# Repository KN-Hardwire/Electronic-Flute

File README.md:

<div align="center">

# Electronic Flute

### *This repository present HARDWIRE student club [AGH University of Cracow](https://en.wikipedia.org/wiki/AGH_University_of_Krak%C3%B3w) Electronic Flute project.*

---

<br />
<em>Watch the video on our YouTube channel to see how it works!</em>

---

</div>

## Programming and assembly

Please refer to guides in each folder for details.

## Playing the flute

All the officially supported note are listed inside the [Fingering Chart](./Fingering_Chart.md), though you should be able to play the instrument just like a standard [recorder flute](https://en.wikipedia.org/wiki/Recorder_(musical_instrument)).

---
<div align="center">
  <sub>Electronic Flute • KN-Hardwire</sub>
</div>

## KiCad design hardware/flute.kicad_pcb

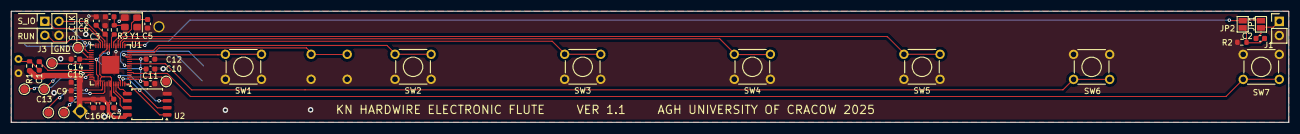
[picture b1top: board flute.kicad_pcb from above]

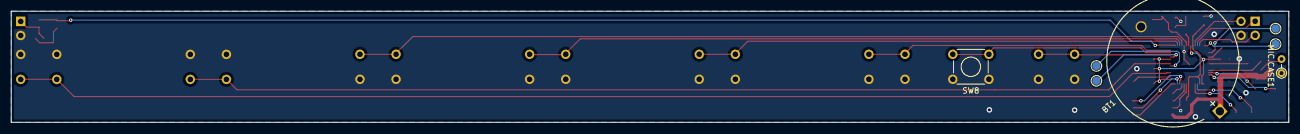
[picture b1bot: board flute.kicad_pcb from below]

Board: 2 copper layers, 230.0 x 20.0 mm, 47 parts (7 on the bottom side), 39 nets.

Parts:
BT1: Battery_Cell; BatteryHolder_MYOUNG_BS-07-A1BJ001_CR2032
C1, C2, C3, C10: 1uF; C_0603_1608Metric
C4, C7, C8, C9, C11, C12, C13, C14, C15, C16: 0.1uF; C_0603_1608Metric
C5, C6: 15pF; C_0603_1608Metric
J1: Conn_01x02; PinHeader_1x02_P2.54mm_Vertical
J3: Conn_01x04; PinHeader_2x02_P2.54mm_Vertical
JP1: COUPLING; SolderJumper-2_P1.3mm_Open_Pad1.0x1.5mm
JP2: NO_COUPLING; SolderJumper-2_P1.3mm_Open_Pad1.0x1.5mm
MIC.CASE1: R; R_Axial_DIN0204_L3.6mm_D1.6mm_P2.54mm_Vertical
R1: 2.2K; R_0603_1608Metric
R2: 100k; R_0603_1608Metric
R3: 1k; R_0603_1608Metric
SW1: C; SW_TH_Tactile_Omron_B3F-100x
SW2: D; SW_TH_Tactile_Omron_B3F-100x
SW3: E; SW_TH_Tactile_Omron_B3F-100x
SW4: F; SW_TH_Tactile_Omron_B3F-100x
SW5: G; SW_TH_Tactile_Omron_B3F-100x
SW6: A; SW_TH_Tactile_Omron_B3F-100x
SW7: H; SW_TH_Tactile_Omron_B3F-100x
SW8: OCTAVE?; SW_TH_Tactile_Omron_B3F-100x
TP2, TP3, TP4, TP5, TP6, TP7, TP8, TP9, TP10, TP11, TP12: TestPoint; TestPoint_Pad_D1.5mm
U1: RP2040; QFN-56-1EP_7x7mm_P0.4mm_EP3.2x3.2mm
U2: W25Q128JVS; SOIC-8_5.3x5.3mm_P1.27mm
Y1: Crystal_GND24; Crystal_SMD_Abracon_ABM8G-4Pin_3.2x2.5mm

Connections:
+1V1: C3.2, C7.1, C8.1, U1.23 (DVDD), U1.45 (VREG_VOUT), U1.50 (DVDD)
+3V3: BT1.1 (+), C4.2, C9.1, C10.1, C11.1, C12.1, C13.1, C14.1, C15.1, C16.1, R1.2, U1.1 (IOVDD), U1.10 (IOVDD), U1.22 (IOVDD), U1.33 (IOVDD), U1.42 (IOVDD), U1.43 (ADC_AVDD), U1.44 (VREG_IN), U1.48 (USB_VDD), U1.49 (IOVDD), U2.8 (VCC)
/KEY_A: SW6.2, U1.8 (GPIO6)
/KEY_C: SW1.2, U1.12 (GPIO9)
/KEY_D: SW2.2, U1.14 (GPIO11)
/KEY_E: SW3.2, U1.16 (GPIO13)
/KEY_F: SW4.2, U1.17 (GPIO14)
/KEY_G: SW5.2, U1.18 (GPIO15)
/KEY_H: SW7.2, U1.4 (GPIO2)
/KEY_OCTAVE: SW8.2, U1.13 (GPIO10)
/MIC_OUTPUT: C1.2, U1.38 (GPIO26_ADC0)
/PWM_OUT: JP1.2 (B), JP2.2 (B), U1.15 (GPIO12)
/RASPBERRY_PI_PICO/QSPI_CS: U1.56 (QSPI_SS), U2.1 (~CS)
/RASPBERRY_PI_PICO/QSPI_SCLK: U1.52 (QSPI_SCLK), U2.6 (CLK)
/RASPBERRY_PI_PICO/QSPI_SD0: U1.53 (QSPI_SD0), U2.5 (DI/IO_{0})
/RASPBERRY_PI_PICO/QSPI_SD1: U1.55 (QSPI_SD1), U2.2 (DO/IO_{1})
/RASPBERRY_PI_PICO/QSPI_SD2: U1.54 (QSPI_SD2), U2.3 (~WP/IO_{2})
/RASPBERRY_PI_PICO/QSPI_SD3: U1.51 (QSPI_SD3), U2.7 (~HOLD/~RESET/IO_{3})
/RASPBERRY_PI_PICO/RUN: J3.3, U1.26 (RUN)
/RASPBERRY_PI_PICO/SWCLK: J3.2, U1.24 (SWCLK)
/RASPBERRY_PI_PICO/SWDIO: J3.1, U1.25 (SWD)
/RASPBERRY_PI_PICO/USB_DM: TP4.1, U1.46 (USB_DM)
/RASPBERRY_PI_PICO/USB_DP: TP3.1, U1.47 (USB_DP)
/RASPBERRY_PI_PICO/XIN: C5.1, U1.20 (XIN), Y1.1
/RASPBERRY_PI_PICO/XOUT: R3.1, U1.21 (XOUT)
GND: BT1.2 (-), C3.1, C4.1, C5.2, C6.2, C7.2, C8.2, C9.2, C10.2, C11.2, C12.2, C13.2, C14.2, C15.2, C16.2, J1.2, J3.4, MIC.CASE1.1, R2.2, SW1.1, SW2.1, SW3.1, SW4.1, SW5.1, SW6.1, SW7.1, SW8.1, U1.19 (TESTEN), U1.57 (GND), U2.4 (GND), Y1.2, Y1.4
unnamed: C1.1, MIC.CASE1.2, R1.1
unnamed: C6.1, R3.2, Y1.3
unnamed: C2.1, J1.1, JP2.1 (A)
unnamed: C2.2, JP1.1 (A), R2.1
unnamed: TP2.1, U1.2 (GPIO0)
unnamed: TP5.1, U1.7 (GPIO5)
unnamed: TP6.1, U1.11 (GPIO8)
unnamed: TP7.1, U1.28 (GPIO17)
unnamed: TP8.1, U1.30 (GPIO19)
unnamed: TP9.1, U1.32 (GPIO21)
unnamed: TP10.1, U1.35 (GPIO23)
unnamed: TP11.1, U1.39 (GPIO27_ADC1)
unnamed: TP12.1, U1.40 (GPIO28_ADC2)

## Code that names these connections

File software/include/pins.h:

#ifndef PINS_H
#define PINS_H

// Pin Configuration for Electronic Flute
#define BUTTON1     ((uint8_t) 9)   // SW1 / KEY_C
#define BUTTON2     ((uint8_t) 11)  // SW2 / KEY_D
#define BUTTON3     ((uint8_t) 13)  // SW3 / KEY_E
#define BUTTON4     ((uint8_t) 14)  // SW4 / KEY_F
#define BUTTON5     ((uint8_t) 15)  // SW5 / KEY_G
#define BUTTON6     ((uint8_t) 6)   // SW6 / KEY_A
#define BUTTON7     ((uint8_t) 2)   // SW7 / KEY_H
#define BUTTON8     ((uint8_t) 10)  // SW8 / KEY_OCTAVE

#define ADC26       ((uint8_t) 26)  // Microphone ADC input
#define OUT_PIN     ((uint8_t) 12)  // Audio PWM output

#endif

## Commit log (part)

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2026-02-23 standardise mask infinite loop bug fix
2026-02-24 slow down work to reduce power consumed
2026-02-28 pin configuration software <-> hardware
2026-02-28 fix button logic
2026-03-01 prototyping volume logic
2026-03-01 clean up
2026-03-01 remove project_type
2026-03-01 refactor get_frequency
2026-03-01 change octave shift
2026-03-01 alpha constant tuned
2026-03-01 fix frequency on all buttons pressed
2026-03-09 Update notes.h
    Fix note definitions and add C#5 for correct flute range
2026-03-09 Update functions.c
    Improve get_frequency comments and semitone calculation
2026-03-11 added license
2026-03-17 custom target for easier flashing with instructions
2026-03-18 added frequency for each button combination for real recorder imitation
2026-03-18 added Fingering Chart
2026-03-18 fixed power issues with flash on pcb
2026-05-24 docs: update readme with video and resized image
2026-05-24 docs: fix video embed in readme
2026-05-24 feat: add video thumbnail asset
2026-05-24 docs: keep only video with a custom caption
